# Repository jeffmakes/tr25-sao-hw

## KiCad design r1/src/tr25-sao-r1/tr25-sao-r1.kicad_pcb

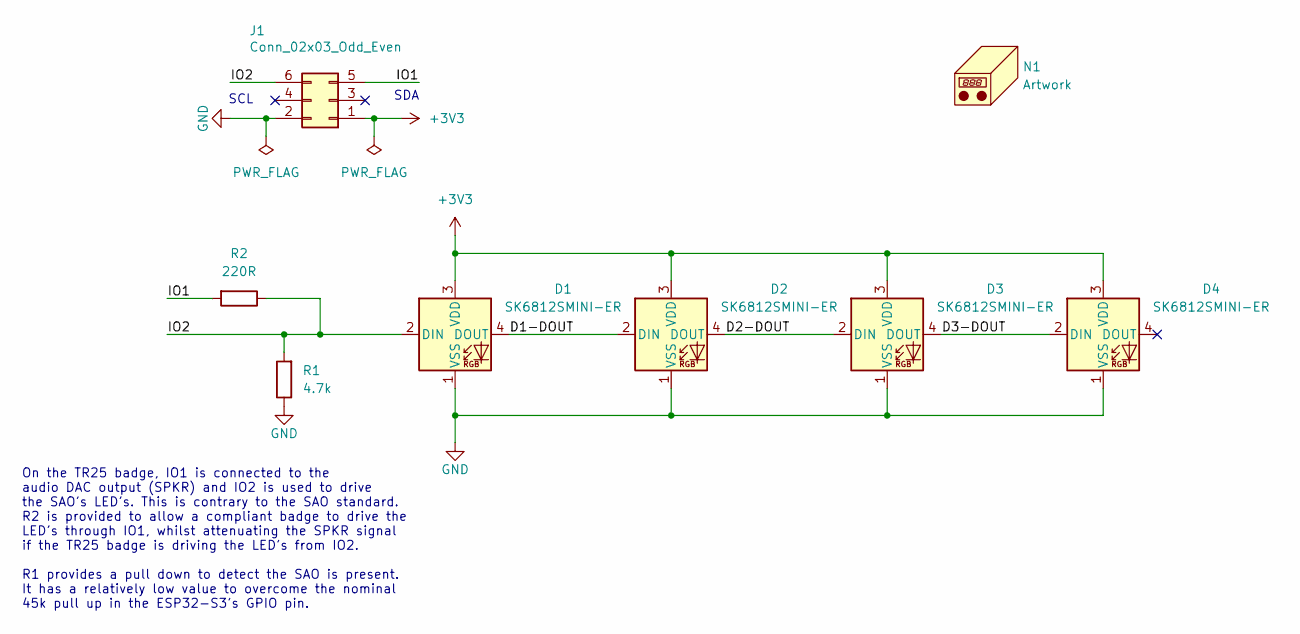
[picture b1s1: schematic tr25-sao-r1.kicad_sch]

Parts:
D1, D2, D3, D4: SK6812SMINI-ER; LED_PLCC4_3.2x2.8mm_CCW
J1: Conn_02x03_Odd_Even; PinHeader_2x03_P2.54mm_Vertical_SMD
N1: Artwork; tr25
R1: 4.7k; R_1206_3216Metric
R2: 220R; R_1206_3216Metric

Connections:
+3V3: D1.3 (VDD), D2.3 (VDD), D3.3 (VDD), D4.3 (VDD), J1.1
/D1-DOUT: D1.4 (DOUT), D2.2 (DIN)
/D2-DOUT: D2.4 (DOUT), D3.2 (DIN)
/D3-DOUT: D3.4 (DOUT), D4.2 (DIN)
/IO1: J1.5, R2.2
/IO2: D1.2 (DIN), J1.6, R1.2, R2.1
GND: D1.1 (VSS), D2.1 (VSS), D3.1 (VSS), D4.1 (VSS), J1.2, R1.1

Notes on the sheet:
On the TR25 badge, IO1 is connected to the audio DAC output (SPKR) and IO2 is used to drive the SAO's LED's. This is contrary to the SAO standard. R2 is provided to allow a compliant badge to drive the LED's through IO1, whilst attenuating the SPKR signal if the TR25 badge is driving the LED's from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
SCL
SDA

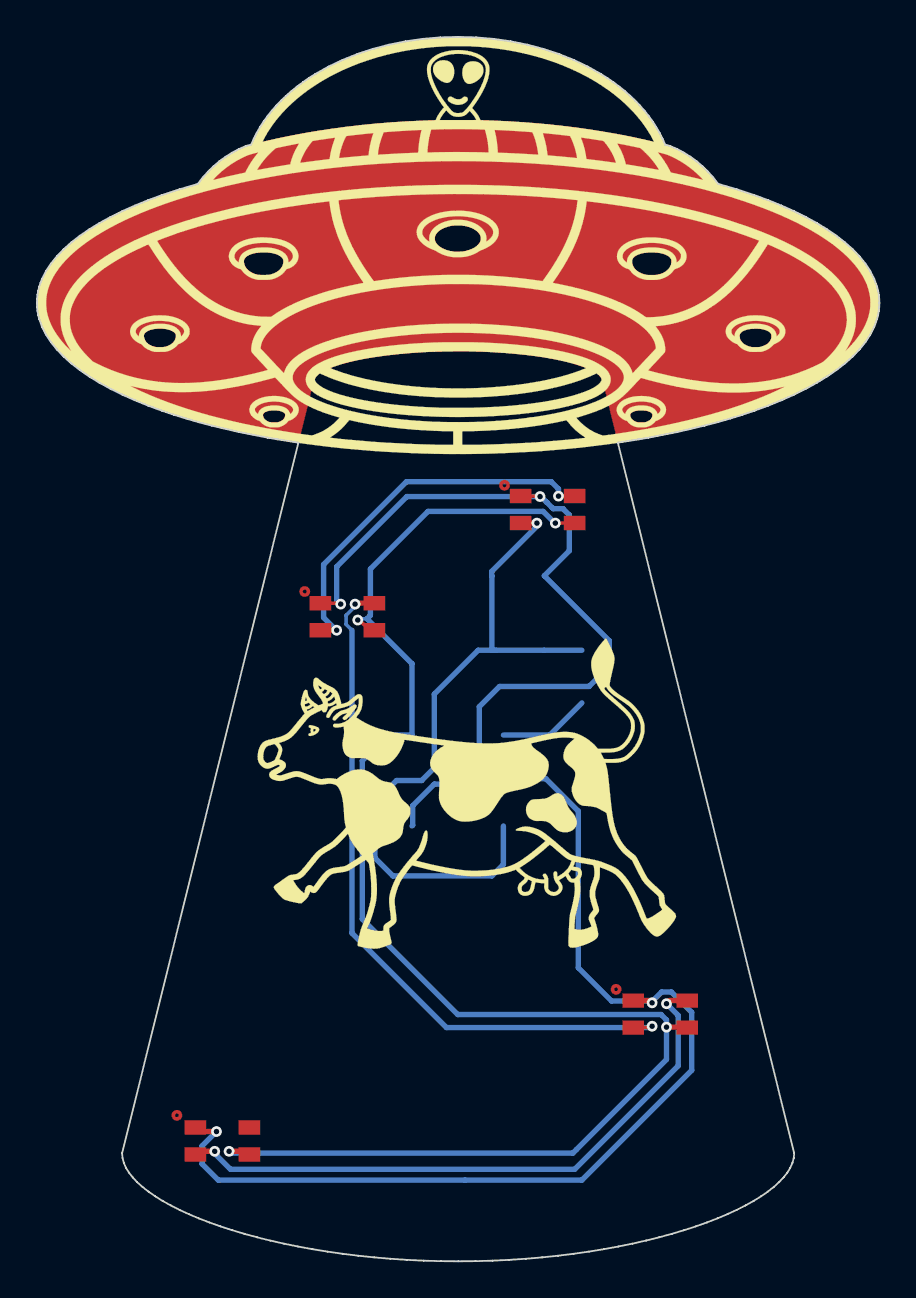
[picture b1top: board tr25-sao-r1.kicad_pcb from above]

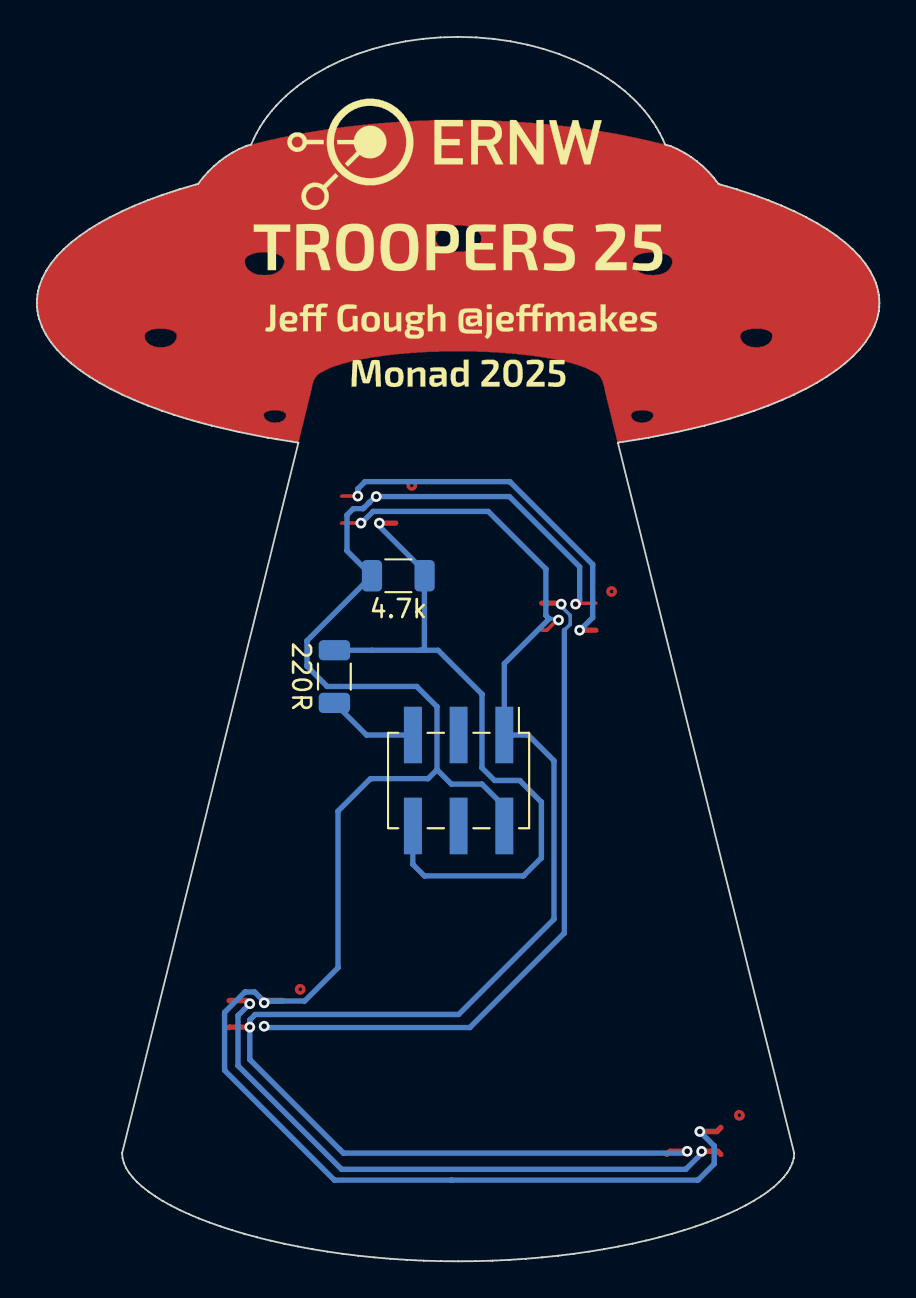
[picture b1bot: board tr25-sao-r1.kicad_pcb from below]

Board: 2 copper layers, 46.8 x 68.0 mm, 8 parts (3 on the bottom side), 7 nets.

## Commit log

2025-06-05 Working on front silk
2025-06-06 Edge cuts, start adding cutouts to F.Mask
2025-06-06 LED Datasheet
2025-06-06 Kicad project
2025-06-06 Artwork footprint import
2025-06-06 Exclude backups
2025-06-06 gitignore backups
2025-06-06 Mask tractor beam
2025-06-06 Add metal
2025-06-06 F.Mask complete. Add rear text and logo
2025-06-07 jeffmakes Kicad library as submodule
2025-06-07 Submodule update
2025-06-07 Add jeffmakes lib to symbol table
2025-06-07 gitignore lock files
2025-06-07 File noise
2025-06-07 Schematic complete, ERC pass
2025-06-07 Assign resistor footprints
2025-06-07 Move rear silk
2025-06-07 Correct LED pinout
2025-06-08 Add soldermask under LED's
2025-06-08 Routing complete. DRC pass
2025-06-08 Production data
2025-06-08 Production data archive
2025-06-08 Add revision number
2025-06-16 PDF's of board and schematic
2025-06-16 All layers in board PDF
